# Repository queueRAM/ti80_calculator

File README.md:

# TI-80 Calculator Reverse Engineering

This repository contains information about the TI-80 graphing calculator hardware and firmware.
Both the main PCB from the TI-80 and the TI-80 ViewScreen capable buffer board are captured.

## Hardware
The hardware architecture contains four main devices: CPU ASIC, external ROM, external RAM,
and LCD controller. These devices are wired together on a shared 8-bit bidirectional parallel bus
and 15 bit address bus. There are separate chip select/chip enable control pins going to the
individual ROM, RAM, LCD modules.

Full schematic is included in this repository along with the notes used to markup the PCB photos.
The schematic is broken into different sections grouping related components. It does not include
all the individual test points, but includes the ones of interest. Full schematic is included in
the repository as [TI-80 schematic PDF](schematics/ti80_schematic_rev1.pdf) or KiCad.

The PCB was reverse engineered using clean photos of the front and back PCB and marking up
the traces in Inkscape and probing individual pins and vias. The marked up document
can be viewed from the repository. It is stored as [TI-80 PCB layers Inkscape SVG](images/ti80_pcb_layers.svg)
with layers.

Additionally, included is the [TI-80 ViewScreen Buffer Board Schematic](ti80_viewscreen_buffer/ti80_viewscreen_buffer.pdf).
This board has two 74HC244 3-state octal buffers which pass take LCD commands sent across a ribbon cable and make
them available to the ViewScreen through the 26-pin ultra thin D-Sub cable.

### Notable Parts:

REFDES | Footprint | Marking   | Manufacturer | Description       | Datasheet?
-------|-----------|-----------|--------------|-------------------|------------
 U1    | PQFP-80   | T6M53A    | Toshiba      | custom CPU ASIC   | None
 U2    | SOP-28    | LH5359    | TI           | external 32KB ROM | None, similar pinout to 23C256 or 27C256
 U3    | SOP-28    | SRM2264LM | Sharp        | external 8KB RAM  | [SRM2264LM](https://www.tautec-electronics.de/Datenblaetter/Schaltkreise/SRM2264LM.pdf)
 U4    | 40-pin    | T6B79     | Toshiba      | LCD controller    | [T6B79](https://datasheet.datasheetarchive.com/originals/distributors/Datasheets-38/DSA-757769.pdf)

### Notable findings:
1. External ROM supports up to 16 address bits, but A15 is tied high so only 32k are accessible
2. Pin 80 is unconnected, but strobes low for the duration of every external bus access (ROM, RAM, LCD)
3. Pin 52 is connected to a pull-up resistor R2 (1MΩ) so likely some sort of input. Tying this to GND doesn’t have obvious side effects
4. Pin 50 is wired out to a test pad, but not anything else. Monitoring it, seems to remain high
5. J5 shorts one of the diodes used for reverse polarity protection. This diode would like cause additional voltage drop and calculator becoming unusable due to the lower voltage powering the LCD
6. Calculator remains powered with only one battery installed, preserving the contents of SRAM. The slide switch in the battery compartment keeps /RST asserted while changing batteries. However, if manually de-asserted, the CPU, RAM, and ROM continue to run properly at 3V. The contrast of the LCD makes it unusable in this state.
7. J17/J18 control which CPU pin is connected to ROM /CE (fitted J17 = pin 18, not-fitted J18 = pin 43)

## Power
Most TI graphing calculators store programs in RAM and use a button cell battery for data retention
while swapping out the main batteries. The TI-80 also stores programs in RAM, but entirely powers
from two CR2032 batteries with no backup battery. Instead, it employs a novel physical switch in
the battery compartment that encourages the user to change one battery at a time and circuitry inside
that can keep the SRAM powered by just one button cell while the batteries are changed, and so
the data is retained. The switch also holds the CPU and LCD in reset by asserting the /RST pin
while the battery compartment slide switch is in the change battery position.

## Firmware
The TI-80 firmware is baked into the ROMs on the calculator and it is not upgradable.
The ROM is split across 16KB embedded inside the main CPU ASIC (marking T6M53A)
and 32KB in the external ROM chip (marking LH5359).

There are two known public versions of the TI-80 firmware: 3.0 and 4.0. The firmware version
can be verified by entering the self-test mode with `Mode` | `Alpha` | `S`. Zeroko's ti80doc
notes, referenced below document the differences between the two ROMs.

## Graph Link
The TI-80 does not contain a graph link port in the consumer retail versions, however, the
ViewScreen enabled version does. The only supported feature of the graph link is requesting
screen shot data. The PCB is the same between both versions, so there are unpopulated pads
in the consumer version for the graph link port and supporting circuitry.

## Notes
Special thanks to Zeroko who have contributed vast knowledge of the TI-80:
* [ti80doc](https://www.ticalc.org/archives/files/fileinfo/442/44236.html) - TI-80 calculator HW/FW documentation
* [ti80emu](https://www.ticalc.org/archives/files/fileinfo/442/44237.html) - TI-80 emulator

### Other notes on TI-80 research and ROM extraction:
* [DataMath | Texas Instruments TI-80 ViewScreen™](http://www.datamath.org/Graphing/TI-80VSC.htm)
* [MAME | TI-80 calculator CPU](https://forums.bannister.org/ubbthreads.php?ubb=showflat&Number=60414)
* [TI Planet | dumping TI-80](https://tiplanet.org/forum/viewtopic.php?f=10&t=5019)
* [Cemetech | Dumping TI-80 ROM directly](https://www.cemetech.net/forum/viewtopic.php?t=20016)
* [Cemetech | TI-80 Hardware Revisions and ViewScreenification™](https://www.cemetech.net/forum/viewtopic.php?t=15350)
* [Silicon Prawn | T6M53A die photos](https://siliconprawn.org/map/toshiba/t6m53a/marmontel_mz_ms20x/)
* [onidev | T6M53A die photos](https://ic.onidev.fr/map/T6M53A.html)

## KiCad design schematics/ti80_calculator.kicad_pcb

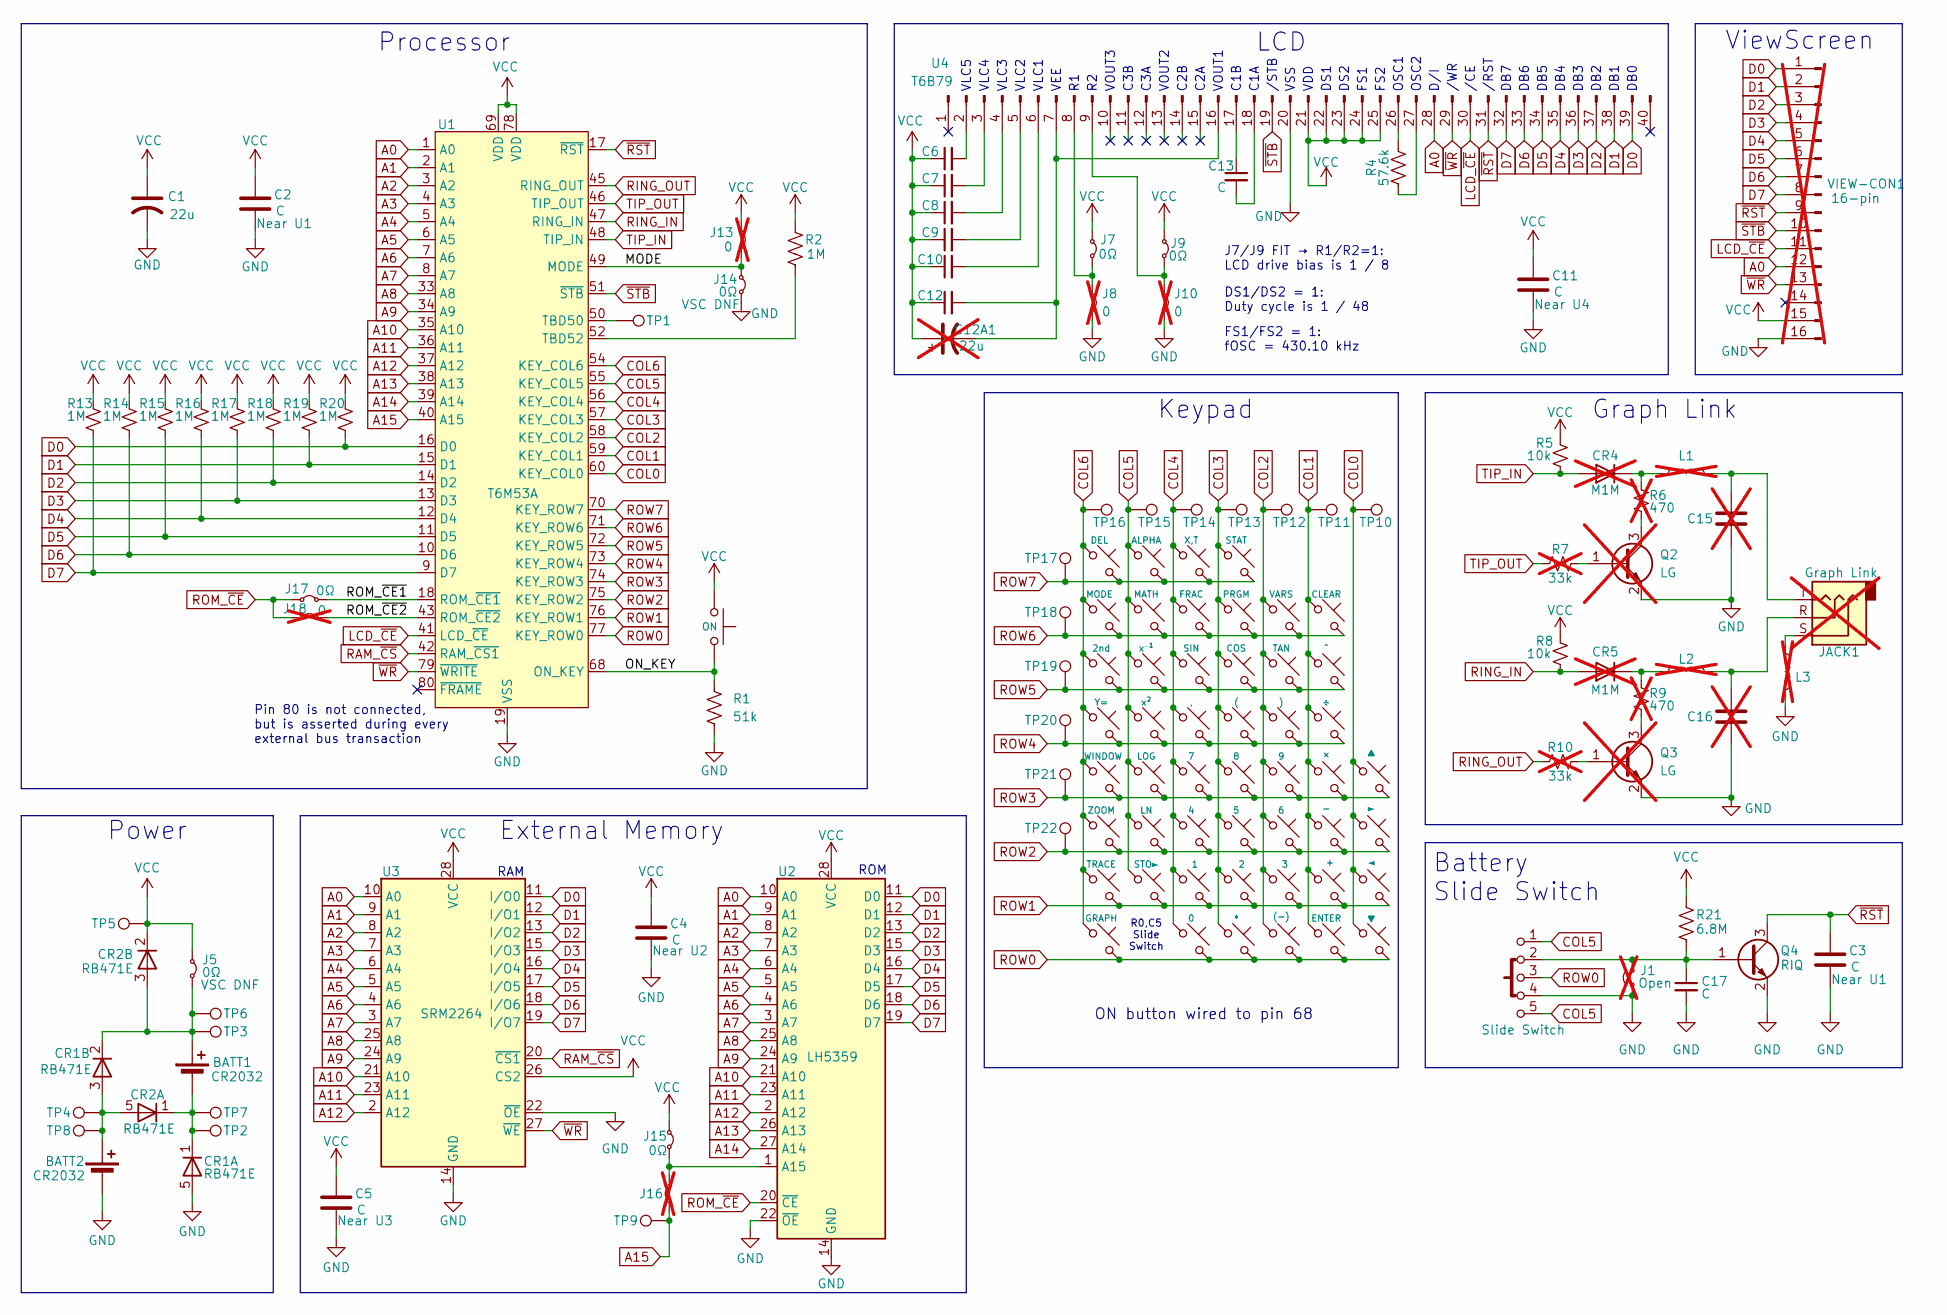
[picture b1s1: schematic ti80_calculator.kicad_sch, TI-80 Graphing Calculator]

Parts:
BATT1, BATT2: CR2032; Battery_Clip_CR2032
C1: 22u; CP_EIA-6032-15_Kemet-U
C2, C3, C4, C5, C6, C7, C8, C9, C10, C11, C12, C13, C17: C; C_0805_2012Metric
C12A1: 22u; CP_EIA-6032-15_Kemet-U; not fitted
C15, C16: C; C_0805_2012Metric; not fitted
CR1, CR2: RB471E; Rohm_SC-74A-5_1.55x2.9mm_P0.95mm
CR4, CR5: M1M; SOT-23; not fitted
J1: Open; R_0805_2012Metric; not fitted
J5, J7, J9, J14, J15, J17: 0Ω; R_0805_2012Metric
J8, J10, J13, J16, J18: 0; R_0805_2012Metric; not fitted
JACK1: Graph Link; Graph_Link_Jack; not fitted
L1, L2, L3: L; L_1008_2520Metric_Pad1.43x2.20mm_HandSolder; not fitted
Q2, Q3: LG; SOT-23-3; not fitted
Q4: RIQ; SOT-323_SC-70_Handsoldering
R1: 51k; R_0805_2012Metric
R2, R13, R14, R15, R16, R17, R18, R19, R20: 1M; R_0805_2012Metric
R4: 57.6k; R_1206_3216Metric
R5, R8: 10k; R_0805_2012Metric
R6, R9: 470; R_0805_2012Metric; not fitted
R7, R10: 33k; R_0805_2012Metric; not fitted
R21: 6.8M; R_0805_2012Metric
SW1: Slide Switch; Switch_Slider_5way
SW2: ON; TI80_Key
SW5: STAT; TI80_Key
SW6: X,T; TI80_Key
SW7: ALPHA; TI80_Key
SW8: DEL; TI80_Key
SW10: CLEAR; TI80_Key
SW11: VARS; TI80_Key
SW12: PRGM; TI80_Key
SW13: FRAC; TI80_Key
SW14: MATH; TI80_Key
SW15: MODE; TI80_Key
SW17: ^; TI80_Key
SW18: TAN; TI80_Key
SW19: COS; TI80_Key
SW20: SIN; TI80_Key
SW21: x⁻¹; TI80_Key
SW22: 2nd; TI80_Key
SW24: ÷; TI80_Key
SW25: ); TI80_Key
SW26: (; TI80_Key
SW27: ,; TI80_Key
SW28: x²; TI80_Key
SW29: Y=; TI80_Key
SW30: ▲; TI80_Key
SW31: ×; TI80_Key
SW32: 9; TI80_Key
SW33: 8; TI80_Key
SW34: 7; TI80_Key
SW35: LOG; TI80_Key
SW36: WINDOW; TI80_Key
SW37: ►; TI80_Key
SW38: -; TI80_Key
SW39: 6; TI80_Key
SW40: 5; TI80_Key
SW41: 4; TI80_Key
SW42: LN; TI80_Key
SW43: ZOOM; TI80_Key
SW44: ◄; TI80_Key
SW45: +; TI80_Key
SW46: 3; TI80_Key
SW47: 2; TI80_Key
SW48: 1; TI80_Key
SW49: STO►; TI80_Key
SW50: TRACE; TI80_Key
SW51: ▼; TI80_Key
SW52: ENTER; TI80_Key
SW53: (-); TI80_Key
SW54: •; TI80_Key
SW55: 0; TI80_Key
SW57: GRAPH; TI80_Key
TP1, TP2, TP3, TP4, TP5, TP6, TP7, TP8, TP9, TP10, TP11, TP12, TP13, TP14, TP15, TP16, TP17, TP18, TP19, TP20, TP21, TP22: Pin 50 Test Point; TestPoint_Pad_D2.0mm
U1: T6M53A; PQFP-80_14x20mm_P0.8mm
U2: LH5359; SOP-28_8.4x18.16mm_P1.27mm
U3: SRM2264; SOP-28_8.4x18.16mm_P1.27mm
U4: T6B79; T6B79_LCD_40pin
VIEW-CON1: 16-pin; TI80_ViewScreen; not fitted

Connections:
/MODE: J13.2 (B), J14.1 (A), U1.49 (MODE)
/ON_KEY: R1.1, SW2.1, U1.68 (ON_KEY); also elsewhere on the board
/ROM_~CE1: J17.2 (B), U1.18 (ROM_~CE1)
/ROM_~CE2: J18.2 (B), U1.43 (ROM_~CE2)
A0: U1.1 (A0), U2.10 (A0), U3.10 (A0), U4.28, VIEW-CON1.12
A1: U1.2 (A1), U2.9 (A1), U3.9 (A1)
A2: U1.3 (A2), U2.8 (A2), U3.8 (A2)
A3: U1.4 (A3), U2.7 (A3), U3.7 (A3)
A4: U1.5 (A4), U2.6 (A4), U3.6 (A4)
A5: U1.6 (A5), U2.5 (A5), U3.5 (A5)
A6: U1.7 (A6), U2.4 (A6), U3.4 (A6)
A7: U1.8 (A7), U2.3 (A7), U3.3 (A7)
A8: U1.33 (A8), U2.25 (A8), U3.25 (A8)
A9: U1.34 (A9), U2.24 (A9), U3.24 (A9)
A10: U1.35 (A10), U2.21 (A10), U3.21 (A10)
A11: U1.36 (A11), U2.23 (A11), U3.23 (A11)
A12: U1.37 (A12), U2.2 (A12), U3.2 (A12)
A13: U1.38 (A13), U2.26 (A13)
A14: U1.39 (A14), U2.27 (A14)
A15: J16.1 (A), TP9.1, U1.40 (A15)
COL0: SW30.1, SW37.1, SW44.1, SW51.1, TP10.1, U1.60 (KEY_COL0)
COL1: SW10.1, SW17.1, SW24.1, SW31.1, SW38.1, SW45.1, SW52.1, TP11.1, U1.59 (KEY_COL1)
COL2: SW11.1, SW18.1, SW25.1, SW32.1, SW39.1, SW46.1, SW53.1, TP12.1, U1.58 (KEY_COL2)
COL3: SW5.1, SW12.1, SW19.1, SW26.1, SW33.1, SW40.1, SW47.1, SW54.1, TP13.1, U1.57 (KEY_COL3)
COL4: SW6.1, SW13.1, SW20.1, SW27.1, SW34.1, SW41.1, SW48.1, SW55.1, TP14.1, U1.56 (KEY_COL4)
COL5: SW1.1, SW1.5, SW7.1, SW14.1, SW21.1, SW28.1, SW35.1, SW42.1, SW49.1, TP15.1, U1.55 (KEY_COL5)
COL6: SW8.1, SW15.1, SW22.1, SW29.1, SW36.1, SW43.1, SW50.1, SW57.1, TP16.1, U1.54 (KEY_COL6)
D0: R20.2, U1.16 (D0), U2.11 (D0), U3.11 (I/O0), U4.39, VIEW-CON1.1
D1: R19.2, U1.15 (D1), U2.12 (D1), U3.12 (I/O1), U4.38, VIEW-CON1.2
D2: R18.2, U1.14 (D2), U2.13 (D2), U3.13 (I/O2), U4.37, VIEW-CON1.3
D3: R17.2, U1.13 (D3), U2.15 (D3), U3.15 (I/O3), U4.36, VIEW-CON1.4
D4: R16.2, U1.12 (D4), U2.16 (D4), U3.16 (I/O4), U4.35, VIEW-CON1.5
D5: R15.2, U1.11 (D5), U2.17 (D5), U3.17 (I/O5), U4.34, VIEW-CON1.6
D6: R14.2, U1.10 (D6), U2.18 (D6), U3.18 (I/O6), U4.33, VIEW-CON1.7
D7: R13.2, U1.9 (D7), U2.19 (D7), U3.19 (I/O7), U4.32, VIEW-CON1.8
GND: BATT2.2 (-), C1.2, C2.2, C3.2, C4.2, C5.2, C11.2, C15.2, C16.2, C17.2, CR1.5, J1.1 (A), J8.2 (B), J10.2 (B), J14.2 (B), L3.2, Q2.2 (E), Q3.2 (E), Q4.2 (E), R1.2, SW1.4, U1.19 (VSS), U2.14 (GND), U2.22 (~OE), U3.14 (GND), U3.22 (~OE), U4.20, VIEW-CON1.16
LCD_~CE: U1.41 (LCD_~CE), U4.30, VIEW-CON1.11
unnamed: BATT1.1 (+), CR1.2, CR2.3, J5.2 (B), TP3.1, TP6.1
unnamed: BATT1.2 (-), CR1.1, CR2.1, TP2.1, TP7.1
unnamed: BATT2.1 (+), CR1.3, CR2.5, TP4.1, TP8.1
unnamed: C15.1, JACK1.T, L1.1
unnamed: C16.1, JACK1.R, L2.1
unnamed: CR4.3 (K), L1.2, R6.1
unnamed: CR5.3 (K), L2.2, R9.1
unnamed: C17.1, J1.2 (B), Q4.1 (B), R21.2, SW1.2
unnamed: J7.2 (B), J8.1 (A), U4.8
unnamed: J9.2 (B), J10.1 (A), U4.9
unnamed: J15.2 (B), J16.2 (B), U2.1 (A15)
unnamed: JACK1.S, L3.1
unnamed: Q2.1 (B), R7.2
unnamed: Q2.3 (C), R6.2
unnamed: Q3.1 (B), R10.2
unnamed: Q3.3 (C), R9.2
unnamed: TP1.1, U1.50 (TBD50)
unnamed: R2.2, U1.52 (TBD52)
unnamed: C6.2, U4.2
unnamed: C7.2, U4.3
unnamed: C8.2, U4.4
unnamed: C9.2, U4.5
unnamed: C10.2, U4.6
unnamed: C12.2, C12A1.2, U4.7, U4.16
unnamed: C13.1, U4.17
unnamed: C13.2, U4.18
unnamed: R4.2, U4.26
unnamed: R4.1, U4.27
RAM_~CS: U1.42 (RAM_~CS1), U3.20 (~CS1)
RING_IN: CR5.1 (A), R8.2, U1.47 (RING_IN)
RING_OUT: R10.1, U1.45 (RING_OUT)
ROM_~CE: J17.1 (A), J18.1 (A), U2.20 (~CE)
ROW0: SW1.3, SW51.2, SW52.2, SW53.2, SW54.2, SW55.2, SW57.2, U1.77 (KEY_ROW0); also elsewhere on the board
ROW1: SW44.2, SW45.2, SW46.2, SW47.2, SW48.2, SW49.2, SW50.2, U1.76 (KEY_ROW1); also elsewhere on the board
ROW2: SW37.2, SW38.2, SW39.2, SW40.2, SW41.2, SW42.2, SW43.2, TP22.1, U1.75 (KEY_ROW2)
ROW3: SW30.2, SW31.2, SW32.2, SW33.2, SW34.2, SW35.2, SW36.2, TP21.1, U1.74 (KEY_ROW3)
ROW4: SW24.2, SW25.2, SW26.2, SW27.2, SW28.2, SW29.2, TP20.1, U1.73 (KEY_ROW4)
ROW5: SW17.2, SW18.2, SW19.2, SW20.2, SW21.2, SW22.2, TP19.1, U1.72 (KEY_ROW5)
ROW6: SW10.2, SW11.2, SW12.2, SW13.2, SW14.2, SW15.2, TP18.1, U1.71 (KEY_ROW6)
ROW7: SW5.2, SW6.2, SW7.2, SW8.2, TP17.1, U1.70 (KEY_ROW7)
TIP_IN: CR4.1 (A), R5.2, U1.48 (TIP_IN)
TIP_OUT: R7.1, U1.46 (TIP_OUT)
VCC: C1.1, C2.1, C4.1, C5.1, C6.1, C7.1, C8.1, C9.1, C10.1, C11.1, C12.1, C12A1.1, CR2.2, J5.1 (A), J7.1 (A), J9.1 (A), J13.1 (A), J15.1 (A), R2.1, R5.1, R8.1, R13.1, R14.1, R15.1, R16.1, R17.1, R18.1, R19.1, R20.1, R21.1, SW2.2, TP5.1, U1.69 (VDD), U1.78 (VDD), U2.28 (VCC), U3.26 (CS2), U3.28 (VCC), U4.21, U4.22, U4.23, U4.24, U4.25, VIEW-CON1.15
~RST: C3.1, Q4.3 (C), U1.17 (~RST), U4.31, VIEW-CON1.9
~STB: U1.51 (~STB), U4.19, VIEW-CON1.10
~WR: U1.79 (~WRITE), U3.27 (~WE), U4.29, VIEW-CON1.13

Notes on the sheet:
VSS
C2B
FS1/FS2 = 1: fOSC = 430.10 kHz
C2A
FS1
DB2
DB3
FS2
C3A
/CE
VOUT1
VLC5
DS1/DS2 = 1: Duty cycle is 1 / 48
VEE
DB6
Keypad
Pin 80 is not connected, but is asserted during every external bus transaction
Processor
ViewScreen
ON button wired to pin 68
/RST
Power
ROM
VOUT2
DS1
RAM
Graph Link
DS2
DB5
VLC2
VOUT3
VLC1
DB7
DB1
D/I
DB0
C1B
Battery Slide Switch
C3B
OSC2

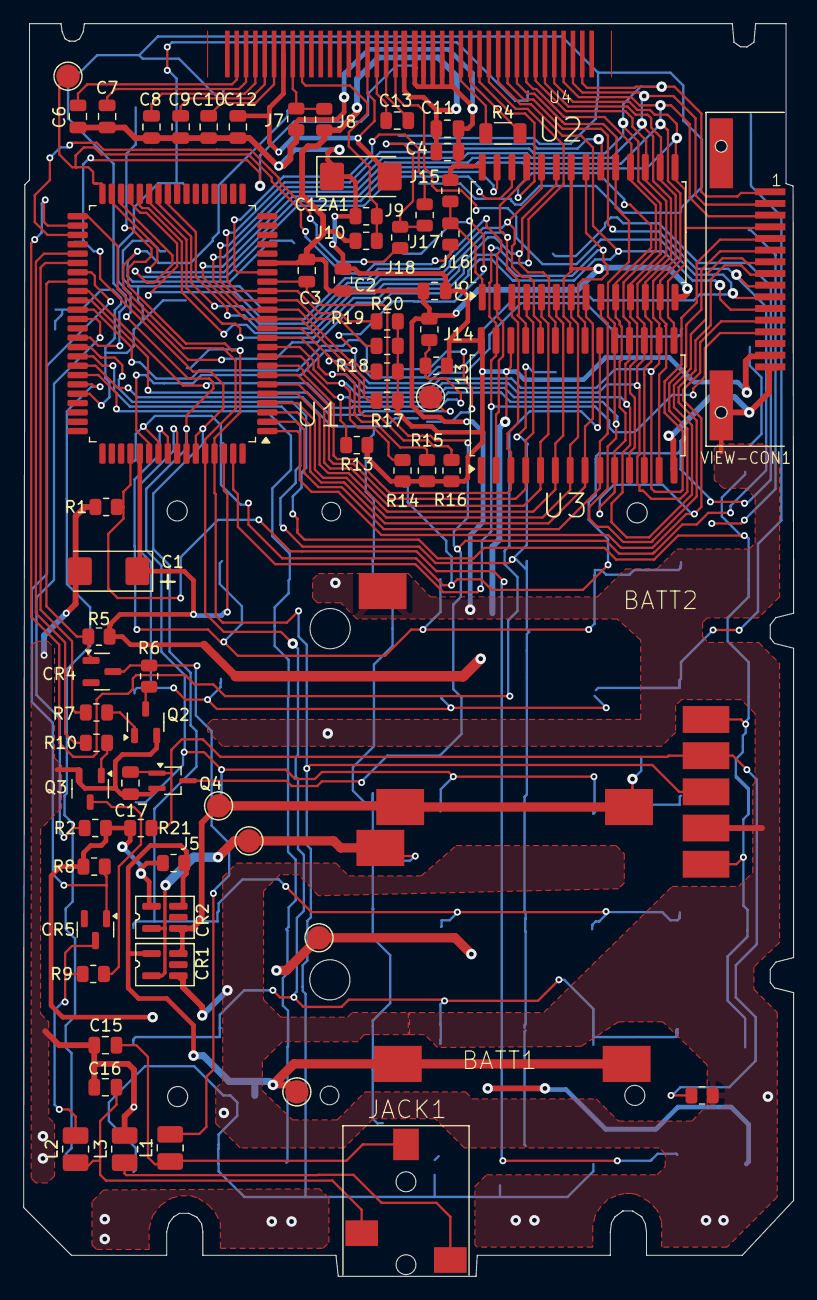
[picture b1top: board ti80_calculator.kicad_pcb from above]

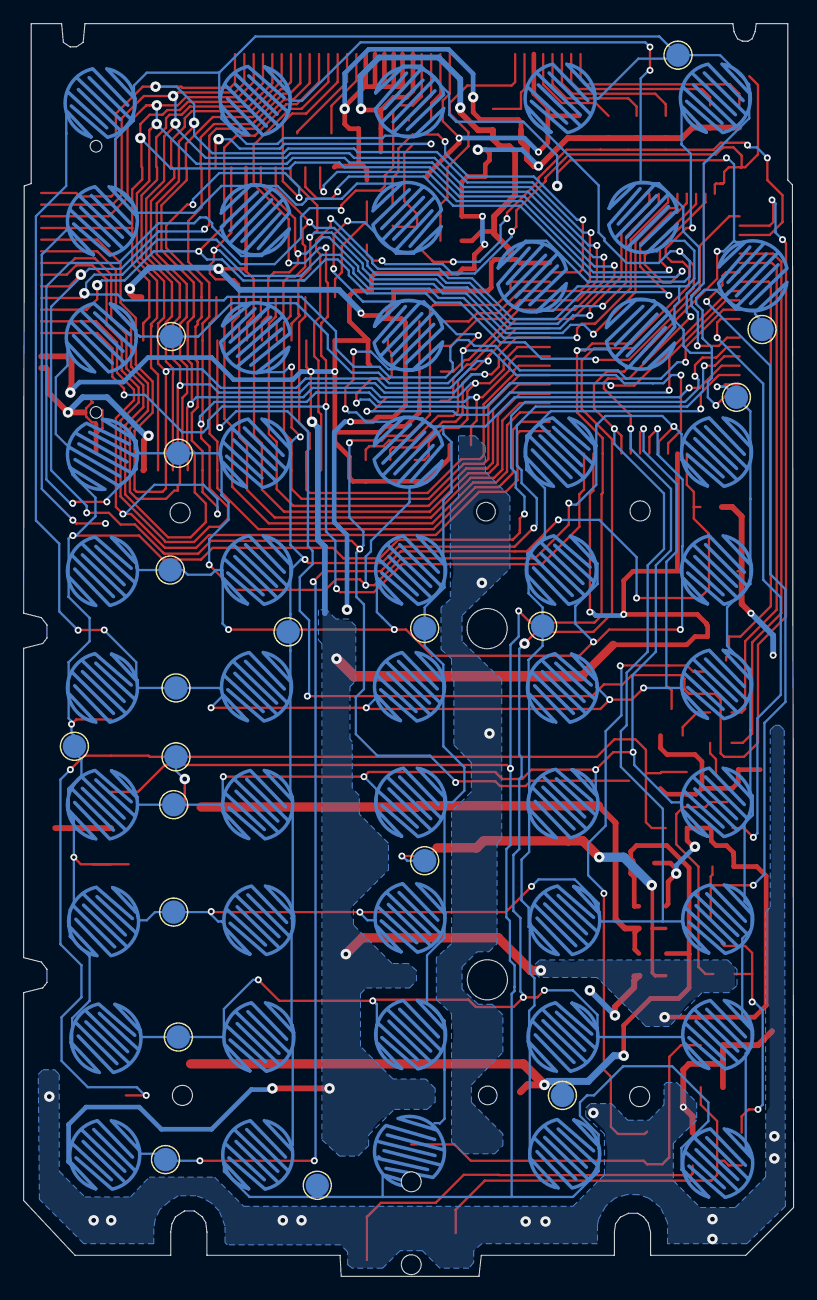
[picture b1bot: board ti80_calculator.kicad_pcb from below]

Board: 2 copper layers, 66.0 x 107.3 mm, 141 parts (69 on the bottom side), 83 nets.

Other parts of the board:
TP23, TP24, TP25: Pin 50 Test Point; TestPoint_Pad_D2.0mm

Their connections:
/ON_KEY: TP25.1; also elsewhere on the board
ROW0: TP24.1; also elsewhere on the board
ROW1: TP23.1; also elsewhere on the board

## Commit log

2025-08-15 Add repository README
2025-08-15 Add Inkscape PCB traces and screenshots of the schematics
2025-08-15 Add TI-80 KiCad schematic, rev 1
2025-08-15 Add multiple layers of the PCB tracing
2025-08-15 Add screenshots of the findings
2025-08-15 Add ASIC Pin 80 logic trace
2025-08-15 Correct left/right arrow key rows to align with ti80doc
2025-08-24 Add custom TI-80 footprints and correct diode and transistor pins
    - Correct diode and transistor pinouts to reflect the packages used
    - Correct some labeling on the schematic
    - Add custom footprints for graph link jack and ViewScreen
    - Create some additional context layers in the PCB SVG
2025-08-24 Add PDF of rev 2 schematic
2025-08-24 Add KiCad PCB layout for TI-80
    Add two layer PCB layout for TI-80 which includes placement and routing of all symbols.
    Keypad footprints still need some work to properly finish routing.
2025-08-24 Update small schematic image to reflect rev 2
2025-08-24 Add .gitignore file
    Ignores KiCad temp and local storage files and macOS .DS_Store
2025-08-24 Make PCB layout orientation portrait and add title and date
2025-08-25 Update key footprint and redo keypad routing
2025-08-25 Add test points for power and keypad
    - Add battery test points on front and back of PCB
    - Add test points for row and columns on keypad side of PCB
2025-08-26 Reorganize the bypass caps and bump rev 3
    - Clean up layout of the U2/U3 capacitors
    - Add more to title and bump revision to 3
2025-09-10 Change inductor package from 1210 to 1008 and hide test point silkscreens
    - 1008 is likely better package size for unpopulated graph link inductors
    - Remove the test point "TP" silkscreen labels
2025-12-31 Add schematic for TI-80 ViewScreen buffer board TIAPLVIS-30C
2026-01-01 Correct pinouts of TI80 viewscreen buffer board
    - 74HC244 is Toshiba which numbers 1-4 and 2nd block starts pin 11
    - 26-pin half pitch ultra thin D-Sub is top-down order
